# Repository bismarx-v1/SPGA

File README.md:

# SPGA
Self playing guitar with a built in amplifier

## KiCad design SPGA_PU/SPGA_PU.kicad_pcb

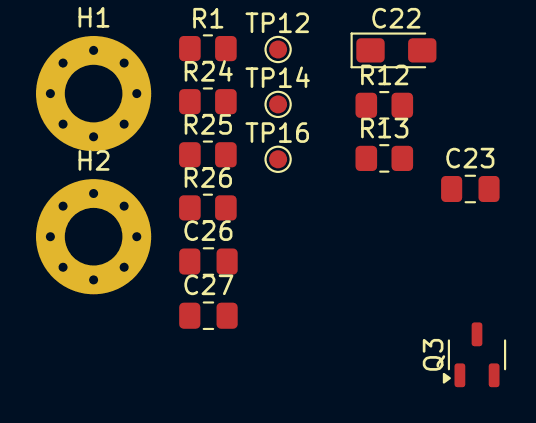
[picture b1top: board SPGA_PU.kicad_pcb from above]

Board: 2 copper layers, 16 parts (0 on the bottom side), 4 nets, no tracks yet.

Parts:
C22: 10uF; CP_EIA-3216-18_Kemet-A_Pad1.58x1.35mm_HandSolder
C23, C26, C27: 100nF; C_0805_2012Metric_Pad1.18x1.45mm_HandSolder
H1, H2: Mounting Hole M3; MountingHole_3.2mm_M3_Pad_Via
Q3: NMOS; SOT-23-3
R1, R12, R13, R24, R25, R26: 10k; R_0805_2012Metric_Pad1.20x1.40mm_HandSolder
TP12, TP14, TP16: TestPoint; TestPoint_Pad_D1.0mm

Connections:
+3V3: C22.1, C23.1, R1.2, R12.2, R13.2, R24.2, R25.1, R26.1, TP14.1
BOOT: C27.1, R1.1
EN: C26.1, R24.1
GND: C22.2, C23.2, C26.2, C27.2, H1.1, H2.1, Q3.2 (S)

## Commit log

2025-06-14 Kicad files
2025-06-15 Schematic updates
2025-06-16 I dunno
2025-07-14 thibgs
